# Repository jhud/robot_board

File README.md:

# Robot controller board

Controller board for building servo-based robots, such as hexapods.

Render of board rev 2

This project was designed to allow rapid prototyping of different types of servos and sensors for walking robots: it's easy to switch out different sensors, and I2C buses are exposed for adding standard plugin components, such as those from Adafruit. But the board could be used for any projects needing a lot of servos.

The main benefit of this over a standard Arduino is the number of PWM pins and the server sockets, plus the power supply monitoring circuitry.

You should be able to get a standard "spiderbot" Arduino sketch running on this hardware quite easily: I'll shortly publish some test sketches and controller firmware.

Have fun!

Board in action

## Features

Core features:
- ESP32 processor, Arduino compatible
- 32 PWM servo channels (ie max 10 legs)
- 6 foot contact sensors
- 7.6v LiPo battery, or power supply input
- Power supply monitoring for:
   - main battery voltage + current
   - 3.3v regulated rail voltage
   - 2x 5v rail servo voltages

With standard plugin modules installed in sockets:
- speech and audio output
- infrared beacon detection
- inertial measurement unit
- extra PWM channels

See it running here (video):

[http://www.youtube.com/watch?v=hFirgdrsIpw](https://www.youtube.com/watch?v=hFirgdrsIpw)

## Building it

### ESP32 CAM

The ESP32 CAM module can run on 3.3v or 5v. If you are getting freezes and dropped frames from the camera, try running it from the robot's 5v rail instead of 3.3v.

The ESP32 CAM has a XC6206-2.8V regulator after its 3.3v regulator, and this component has a dropout voltage up to ~500mV according to the specs. My hypothesis is that the camera crashes on slight undervoltages.

So the 3.3v rail must be rock solid - this may not be the case with your regulator, so it's generally recommended to run the ESP32 CAM off the 5v rail. Even with many noisy servos, the camera works fine on the robot on the 5v rail.

### Pullup resistors

Pullups can vary between 2K and 10K - if there are problems communicating with I2C, try reducing the pullups. Higher pull-ups waste less power.

## Revisions

Note that the main branch is a work in progress: please take an earlier revision if you want a working layout. These are tested and working (with some minor noise issues and a couple of bodge wires needed).

- main branch is a work in progress: I am upgrading to ESP32-S3 and have fixed some noise issues and minor annoyances. Use an older tag if you want something that works.
- 2nd revision: 32 PWM channels onboard, 6 foot switches + power pins for IR proximity sensors
- 1st revision: 16 PWM channels, 4 foot switches

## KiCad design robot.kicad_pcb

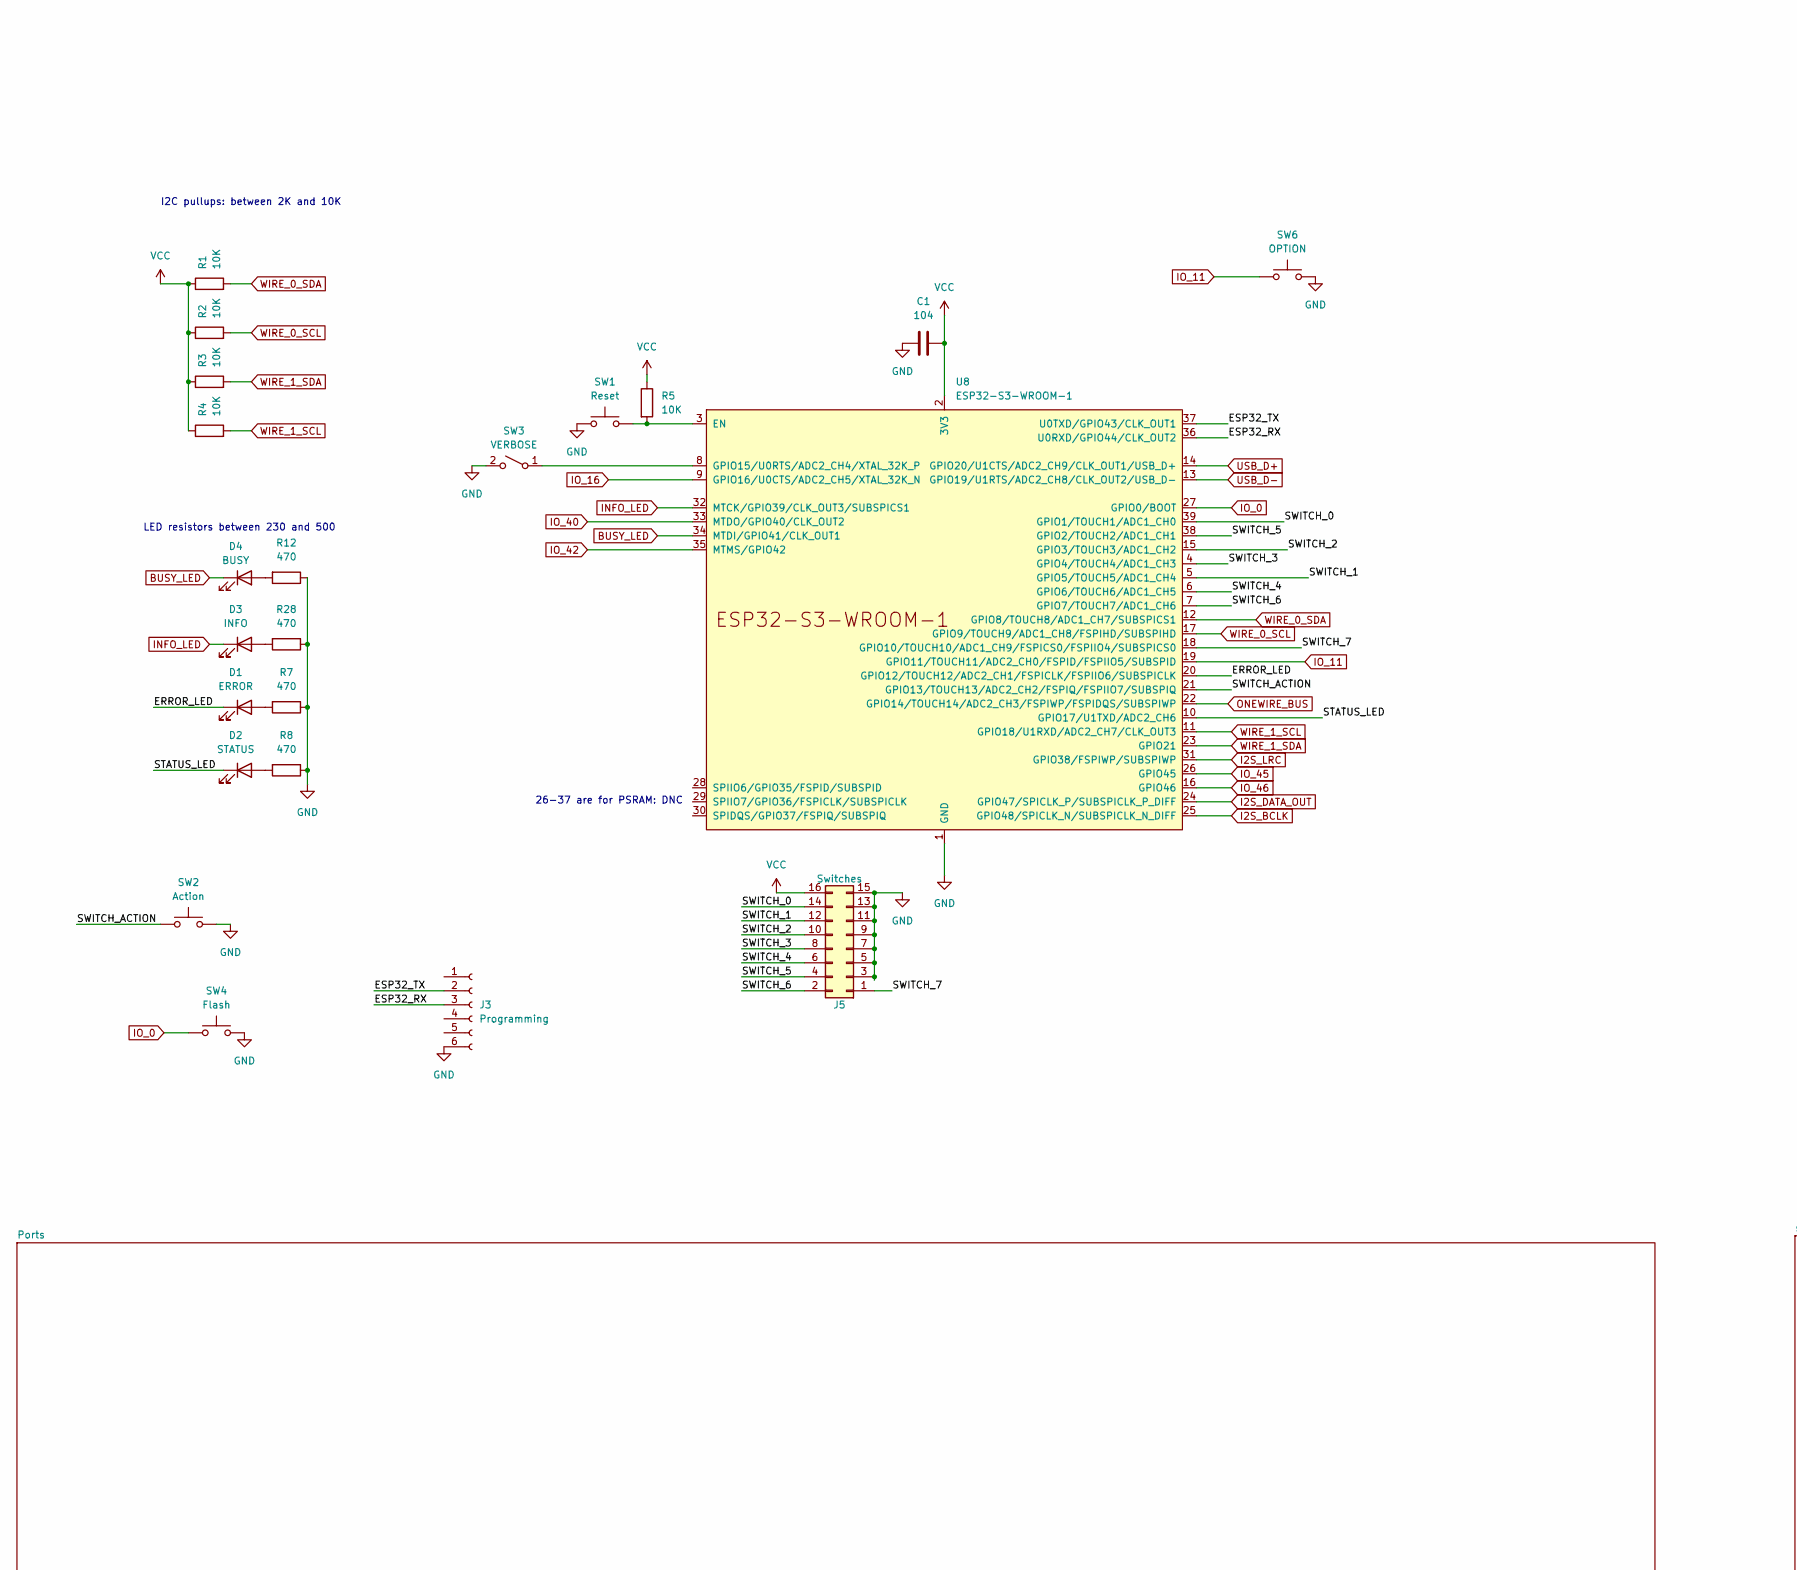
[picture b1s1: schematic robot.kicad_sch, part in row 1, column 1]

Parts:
C1: 104; C_1206_3216Metric_Pad1.33x1.80mm_HandSolder
D1: ERROR; LED_1206_3216Metric_Pad1.42x1.75mm_HandSolder
D2: STATUS; LED_1206_3216Metric_Pad1.42x1.75mm_HandSolder
D3: INFO; LED_1206_3216Metric_Pad1.42x1.75mm_HandSolder
D4: BUSY; LED_1206_3216Metric_Pad1.42x1.75mm_HandSolder
J3: Programming; PinSocket_1x06_P2.54mm_Vertical
J5: Switches; PinSocket_2x08_P2.54mm_Vertical
R1, R2, R3, R4, R5: 10K; R_1206_3216Metric_Pad1.30x1.75mm_HandSolder
R7, R8, R12, R28: 470; R_1206_3216Metric_Pad1.30x1.75mm_HandSolder
SW1: Reset; SW_SPST_CK_RS282G05A3
SW2: Action; SW_SPST_CK_RS282G05A3
SW3: VERBOSE; SW_Slide_1P2T_CK_OS102011MS2Q
SW4: Flash; SW_SPST_CK_RS282G05A3
SW6: OPTION; SW_SPST_CK_RS282G05A3
U8: ESP32-S3-WROOM-1; ESP32-S3-WROOM-1U

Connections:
/ERROR_LED: D1.1 (K), U8.20 (GPIO12/TOUCH12/ADC2_CH1/FSPICLK/FSPIIO6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)
/ESP32_RX: J3.3, U8.36 (U0RXD/GPIO44/CLK_OUT2)
/ESP32_TX: J3.2, U8.37 (U0TXD/GPIO43/CLK_OUT1)
/STATUS_LED: D2.1 (K), U8.10 (GPIO17/U1TXD/ADC2_CH6)
/SWITCH_0: J5.14, U8.39 (GPIO1/TOUCH1/ADC1_CH0)
/SWITCH_1: J5.12, U8.5 (GPIO5/TOUCH5/ADC1_CH4)
/SWITCH_2: J5.10, U8.15 (GPIO3/TOUCH3/ADC1_CH2)
/SWITCH_3: J5.8, U8.4 (GPIO4/TOUCH4/ADC1_CH3)
/SWITCH_4: J5.6, U8.6 (GPIO6/TOUCH6/ADC1_CH5)
/SWITCH_5: J5.4, U8.38 (GPIO2/TOUCH2/ADC1_CH1)
/SWITCH_6: J5.2, U8.7 (GPIO7/TOUCH7/ADC1_CH6)
/SWITCH_7: J5.1, U8.18 (GPIO10/TOUCH10/ADC1_CH9/FSPICS0/FSPIIO4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)
/SWITCH_ACTION: SW2.1, U8.21 (GPIO13/TOUCH13/ADC2_CH2/FSPIQ/FSPIIO7/S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)
BUSY_LED: D4.1 (K), U8.34 (MTDI/GPIO41/CLK_OUT1)
GND: C1.1, J3.6, J5.3, J5.5, J5.7, J5.9, J5.11, J5.13, J5.15, R7.1, R8.1, R12.1, R28.1, SW1.1, SW2.2, SW3.2 (B), SW4.2, SW6.2, U8.1 (GND), U8.40 (GND), U8.41 (GND); also elsewhere on the board
I2S_BCLK: U8.25 (GPIO48/SPICLK_N/SUBSPICLK_N_DIFF); also elsewhere on the board
I2S_DATA_OUT: U8.24 (GPIO47/SPICLK_P/SUBSPICLK_P_DIFF); also elsewhere on the board
I2S_LRC: U8.31 (GPIO38/FSPIWP/SUBSPIWP); also elsewhere on the board
INFO_LED: D3.1 (K), U8.32 (MTCK/GPIO39/CLK_OUT3/SUBSPICS1)
IO_0: SW4.1, U8.27 (GPIO0/BOOT)
IO_11: SW6.1, U8.19 (GPIO11/TOUCH11/ADC2_CH0/FSPID/FSPIIO5/S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)
IO_16: U8.9 (GPIO16/U0CTS/ADC2_CH5/XTAL_32K_N); also elsewhere on the board
IO_40: U8.33 (MTDO/GPIO40/CLK_OUT2); also elsewhere on the board
IO_42: U8.35 (MTMS/GPIO42); also elsewhere on the board
IO_45: U8.26 (GPIO45); also elsewhere on the board
IO_46: U8.16 (GPIO46); also elsewhere on the board
unnamed: D1.2 (A), R7.2
unnamed: D2.2 (A), R8.2
unnamed: D3.2 (A), R28.2
unnamed: D4.2 (A), R12.2
unnamed: SW3.1 (A), U8.8 (GPIO15/U0RTS/ADC2_CH4/XTAL_32K_P)
unnamed: R5.2, SW1.2, U8.3 (EN)
ONEWIRE_BUS: U8.22 (GPIO14/TOUCH14/ADC2_CH3/FSPIWP/FSPIDQS/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); also elsewhere on the board
USB_D+: U8.14 (GPIO20/U1CTS/ADC2_CH9/CLK_OUT1/USB_D+); also elsewhere on the board
USB_D-: U8.13 (GPIO19/U1RTS/ADC2_CH8/CLK_OUT2/USB_D-); also elsewhere on the board
VCC: C1.2, J5.16, R1.1, R2.1, R3.1, R4.1, R5.1, U8.2 (3V3); also elsewhere on the board
WIRE_0_SCL: R2.2, U8.17 (GPIO9/TOUCH9/ADC1_CH8/FSPIHD/SUBSPIHD); also elsewhere on the board
WIRE_0_SDA: R1.2, U8.12 (GPIO8/TOUCH8/ADC1_CH7/SUBSPICS1); also elsewhere on the board

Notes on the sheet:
26-37 are for PSRAM: DNC
LED resistors between 230 and 500
I2C pullups: between 2K and 10K

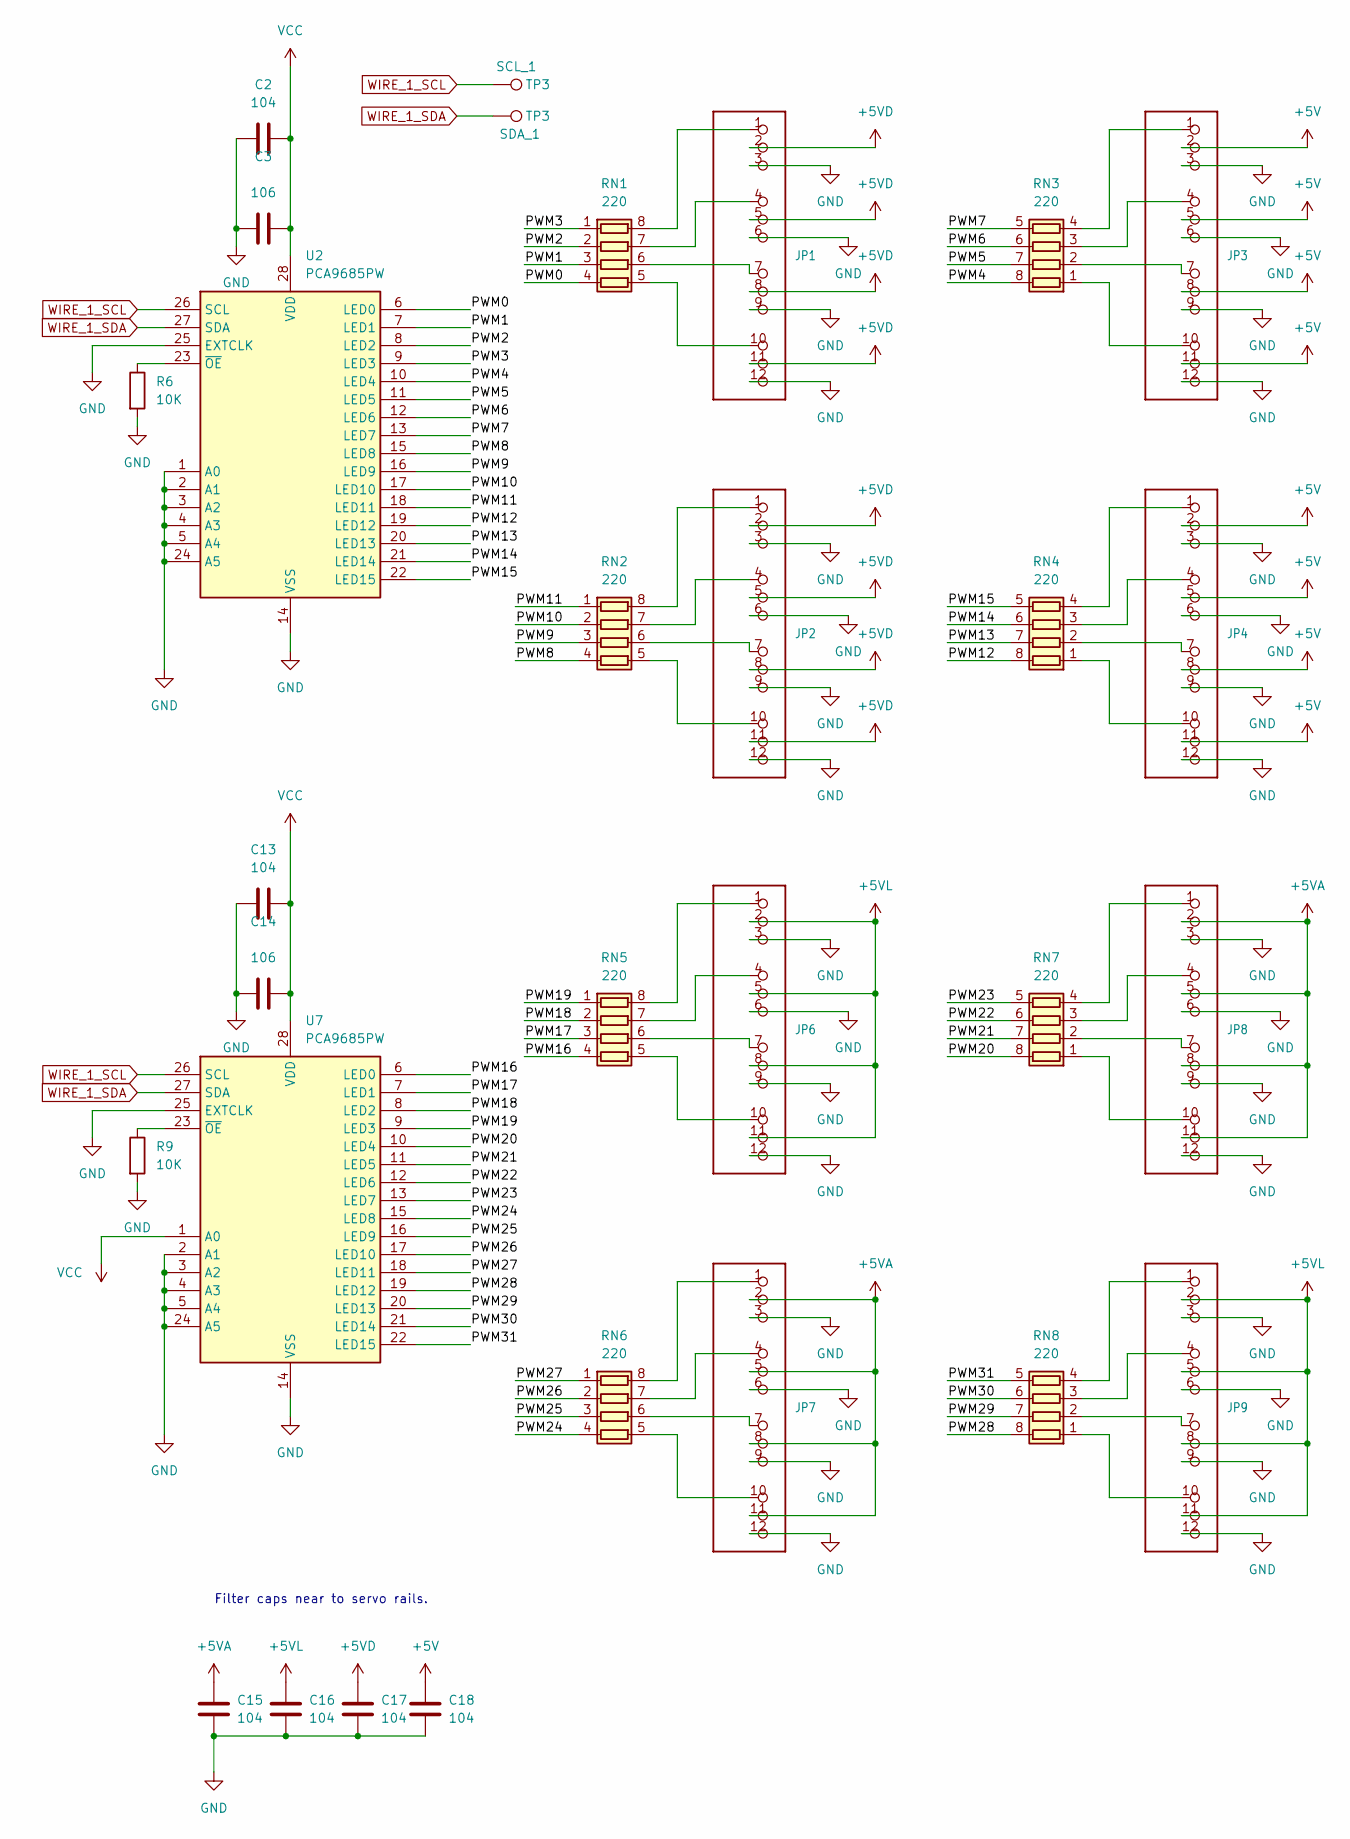
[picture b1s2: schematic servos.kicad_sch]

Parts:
C2, C13, C15, C16, C17, C18: 104; C_1206_3216Metric_Pad1.33x1.80mm_HandSolder
C3, C14: 106; C_1210_3225Metric_Pad1.33x2.70mm_HandSolder
JP1, JP2, JP3, JP4, JP6, JP7, JP8, JP9: HEADER-3X04; 3X04
R6, R9: 10K; R_1206_3216Metric_Pad1.30x1.75mm_HandSolder
RN1, RN2, RN3, RN4, RN5, RN6, RN7, RN8: 220; R_Array_Concave_4x0603
TP3: SCL_1; TestPoint_Pad_D2.0mm
U2, U7: PCA9685PW; TSSOP-28_4.4x9.7mm_P0.65mm

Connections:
+5V: C18.1, JP3.2, JP3.5, JP3.8, JP3.11, JP4.2, JP4.5, JP4.8, JP4.11; also elsewhere on the board
+5VD: C17.1, JP1.2, JP1.5, JP1.8, JP1.11, JP2.2, JP2.5, JP2.8, JP2.11; also elsewhere on the board
+5VL: C16.1, JP6.2, JP6.5, JP6.8, JP6.11, JP9.2, JP9.5, JP9.8, JP9.11; also elsewhere on the board
/servos/PWM0: RN1.4 (R4.1), U2.6 (LED0)
/servos/PWM1: RN1.3 (R3.1), U2.7 (LED1)
/servos/PWM2: RN1.2 (R2.1), U2.8 (LED2)
/servos/PWM3: RN1.1 (R1.1), U2.9 (LED3)
/servos/PWM4: RN3.8 (R1.2), U2.10 (LED4)
/servos/PWM5: RN3.7 (R2.2), U2.11 (LED5)
/servos/PWM6: RN3.6 (R3.2), U2.12 (LED6)
/servos/PWM7: RN3.5 (R4.2), U2.13 (LED7)
/servos/PWM8: RN2.4 (R4.1), U2.15 (LED8)
/servos/PWM9: RN2.3 (R3.1), U2.16 (LED9)
/servos/PWM10: RN2.2 (R2.1), U2.17 (LED10)
/servos/PWM11: RN2.1 (R1.1), U2.18 (LED11)
/servos/PWM12: RN4.8 (R1.2), U2.19 (LED12)
/servos/PWM13: RN4.7 (R2.2), U2.20 (LED13)
/servos/PWM14: RN4.6 (R3.2), U2.21 (LED14)
/servos/PWM15: RN4.5 (R4.2), U2.22 (LED15)
/servos/PWM16: RN5.4 (R4.1), U7.6 (LED0)
/servos/PWM17: RN5.3 (R3.1), U7.7 (LED1)
/servos/PWM18: RN5.2 (R2.1), U7.8 (LED2)
/servos/PWM19: RN5.1 (R1.1), U7.9 (LED3)
/servos/PWM20: RN7.8 (R1.2), U7.10 (LED4)
/servos/PWM21: RN7.7 (R2.2), U7.11 (LED5)
/servos/PWM22: RN7.6 (R3.2), U7.12 (LED6)
/servos/PWM23: RN7.5 (R4.2), U7.13 (LED7)
/servos/PWM24: RN6.4 (R4.1), U7.15 (LED8)
/servos/PWM25: RN6.3 (R3.1), U7.16 (LED9)
/servos/PWM26: RN6.2 (R2.1), U7.17 (LED10)
/servos/PWM27: RN6.1 (R1.1), U7.18 (LED11)
/servos/PWM28: RN8.8 (R1.2), U7.19 (LED12)
/servos/PWM29: RN8.7 (R2.2), U7.20 (LED13)
/servos/PWM30: RN8.6 (R3.2), U7.21 (LED14)
/servos/PWM31: RN8.5 (R4.2), U7.22 (LED15)
GND: C2.2, C3.1, C13.2, C14.1, C15.2, C16.2, C17.2, C18.2, JP1.3, JP1.6, JP1.9, JP1.12, JP2.3, JP2.6, JP2.9, JP2.12, JP3.3, JP3.6, JP3.9, JP3.12, JP4.3, JP4.6, JP4.9, JP4.12, JP6.3, JP6.6, JP6.9, JP6.12, JP7.3, JP7.6, JP7.9, JP7.12, JP8.3, JP8.6, JP8.9, JP8.12, JP9.3, JP9.6, JP9.9, JP9.12, R6.2, R9.2, U2.1 (A0), U2.2 (A1), U2.3 (A2), U2.4 (A3), U2.5 (A4), U2.14 (VSS), U2.24 (A5), U2.25 (EXTCLK), U7.2 (A1), U7.3 (A2), U7.4 (A3), U7.5 (A4), U7.14 (VSS), U7.24 (A5), U7.25 (EXTCLK); also elsewhere on the board
unnamed: JP1.1, RN1.8 (R1.2)
unnamed: JP1.4, RN1.7 (R2.2)
unnamed: JP1.7, RN1.6 (R3.2)
unnamed: JP1.10, RN1.5 (R4.2)
unnamed: JP2.1, RN2.8 (R1.2)
unnamed: JP2.4, RN2.7 (R2.2)
unnamed: JP2.7, RN2.6 (R3.2)
unnamed: JP2.10, RN2.5 (R4.2)
unnamed: JP3.10, RN3.1 (R1.1)
unnamed: JP3.7, RN3.2 (R2.1)
unnamed: JP3.4, RN3.3 (R3.1)
unnamed: JP3.1, RN3.4 (R4.1)
unnamed: JP4.10, RN4.1 (R1.1)
unnamed: JP4.7, RN4.2 (R2.1)
unnamed: JP4.4, RN4.3 (R3.1)
unnamed: JP4.1, RN4.4 (R4.1)
unnamed: JP6.1, RN5.8 (R1.2)
unnamed: JP6.4, RN5.7 (R2.2)
unnamed: JP6.7, RN5.6 (R3.2)
unnamed: JP6.10, RN5.5 (R4.2)
unnamed: JP7.1, RN6.8 (R1.2)
unnamed: JP7.4, RN6.7 (R2.2)
unnamed: JP7.7, RN6.6 (R3.2)
unnamed: JP7.10, RN6.5 (R4.2)
unnamed: JP8.10, RN7.1 (R1.1)
unnamed: JP8.7, RN7.2 (R2.1)
unnamed: JP8.4, RN7.3 (R3.1)
unnamed: JP8.1, RN7.4 (R4.1)
unnamed: JP9.10, RN8.1 (R1.1)
unnamed: JP9.7, RN8.2 (R2.1)
unnamed: JP9.4, RN8.3 (R3.1)
unnamed: JP9.1, RN8.4 (R4.1)
unnamed: R6.1, U2.23 (~OE)
unnamed: R9.1, U7.23 (~OE)
VCC: C2.1, C3.2, C13.1, C14.2, U2.28 (VDD), U7.1 (A0), U7.28 (VDD); also elsewhere on the board

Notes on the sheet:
Filter caps near to servo rails.

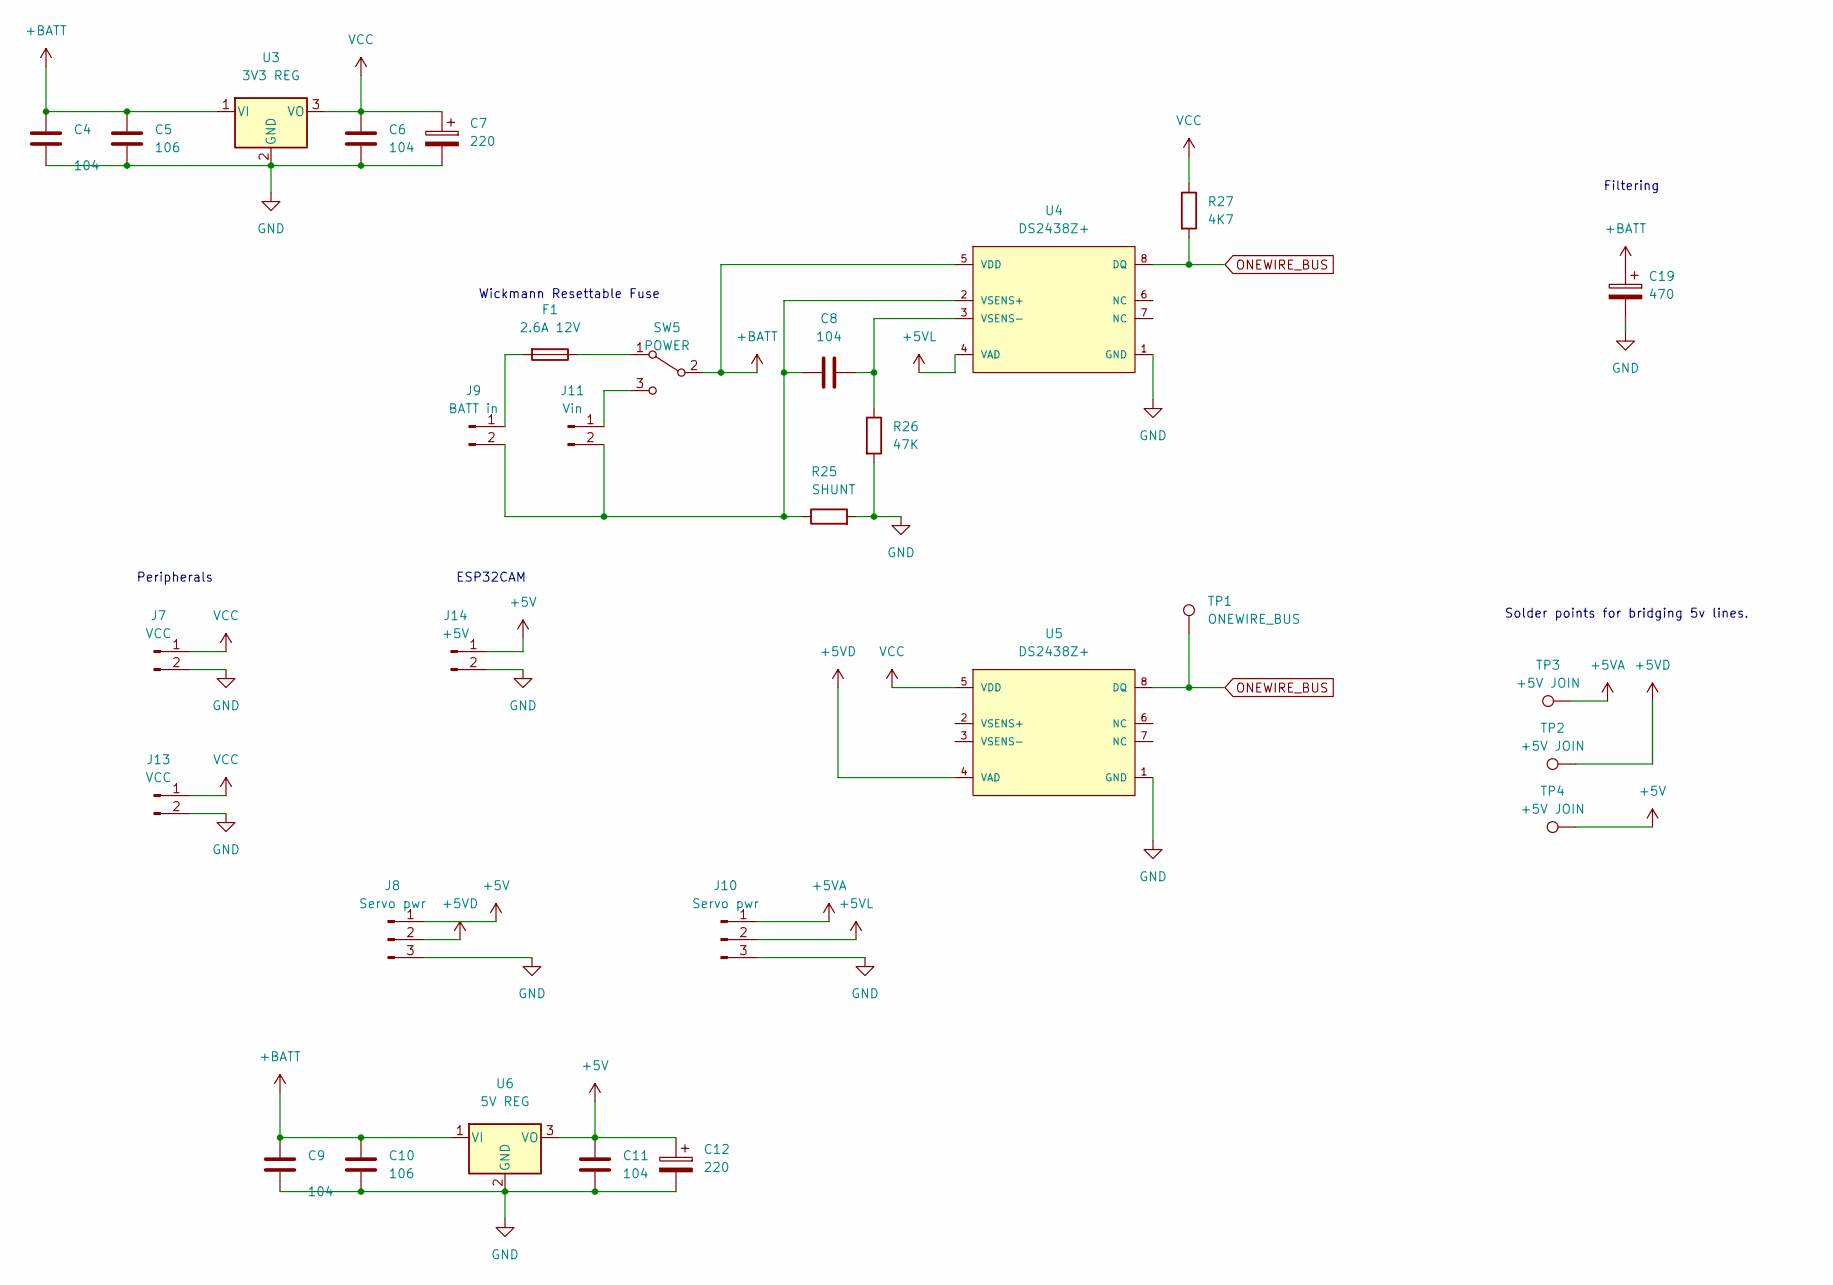
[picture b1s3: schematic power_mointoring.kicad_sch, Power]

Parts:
C4, C6, C8, C9, C11: 104; C_1206_3216Metric_Pad1.33x1.80mm_HandSolder
C5, C10: 106; C_1210_3225Metric_Pad1.33x2.70mm_HandSolder
C7, C12: 220; C_Elec_6.3x5.4
C19: 470; C_Elec_6.3x7.7
F1: 2.6A 12V; Fuse_2010_5025Metric
J7, J13: VCC; PinHeader_1x02_P2.54mm_Vertical
J8, J10: Servo pwr; Connector_SolderPadsx3
J9: BATT in; JST_VH_B2P-VH-B_1x02_P3.96mm_Vertical
J11: Vin; JST_VH_B2P-VH-B_1x02_P3.96mm_Vertical
J14: +5V; PinHeader_1x02_P2.54mm_Vertical
R25: SHUNT; R_1812_4532Metric_Pad1.30x3.40mm_HandSolder
R26: 47K; R_1206_3216Metric_Pad1.30x1.75mm_HandSolder
R27: 4K7; R_1206_3216Metric_Pad1.30x1.75mm_HandSolder
SW5: POWER; Switch-SS12F23
TP1: ONEWIRE_BUS; TestPoint_Pad_D2.0mm
TP2, TP3, TP4: +5V JOIN; TestPoint_Pad_D2.0mm
U3: 3V3 REG; TO-220-3_Vertical
U4, U5: DS2438Z+; Maxim-S8-5-0-P-IPC_A; mouser part number 700-DS2438Z; digikey description IC MONITOR SMART BATTERY 8-SOIC
U6: 5V REG; TO-220-3_Vertical

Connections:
+5V: C11.1, C12.1, J8.1, J14.1, TP4.1, U6.3 (VO); also elsewhere on the board
+5VD: J8.2, TP2.1, U5.4 (VAD); also elsewhere on the board
+5VL: J10.2, U4.4 (VAD); also elsewhere on the board
+BATT: C4.1, C5.1, C9.1, C10.1, C19.1, SW5.2 (B), U3.1 (VI), U4.5 (VDD), U6.1 (VI)
GND: C4.2, C5.2, C6.2, C7.2, C9.2, C10.2, C11.2, C12.2, C19.2, J7.2, J8.3, J10.3, J13.2, J14.2, R25.2, R26.2, U3.2 (GND), U4.1 (GND), U5.1 (GND), U6.2 (GND); also elsewhere on the board
unnamed: F1.2, J9.1
unnamed: J11.1, SW5.3 (C)
unnamed: C8.2, J9.2, J11.2, R25.1, U4.2 (VSENS+)
unnamed: F1.1, SW5.1 (A)
unnamed: C8.1, R26.1, U4.3 (VSENS-)
ONEWIRE_BUS: R27.2, TP1.1, U4.8 (DQ), U5.8 (DQ); also elsewhere on the board
VCC: C6.1, C7.1, J7.1, J13.1, R27.1, U3.3 (VO), U5.5 (VDD); also elsewhere on the board

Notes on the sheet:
Filtering
ESP32CAM
Solder points for bridging 5v lines.
Wickmann Resettable Fuse
Peripherals

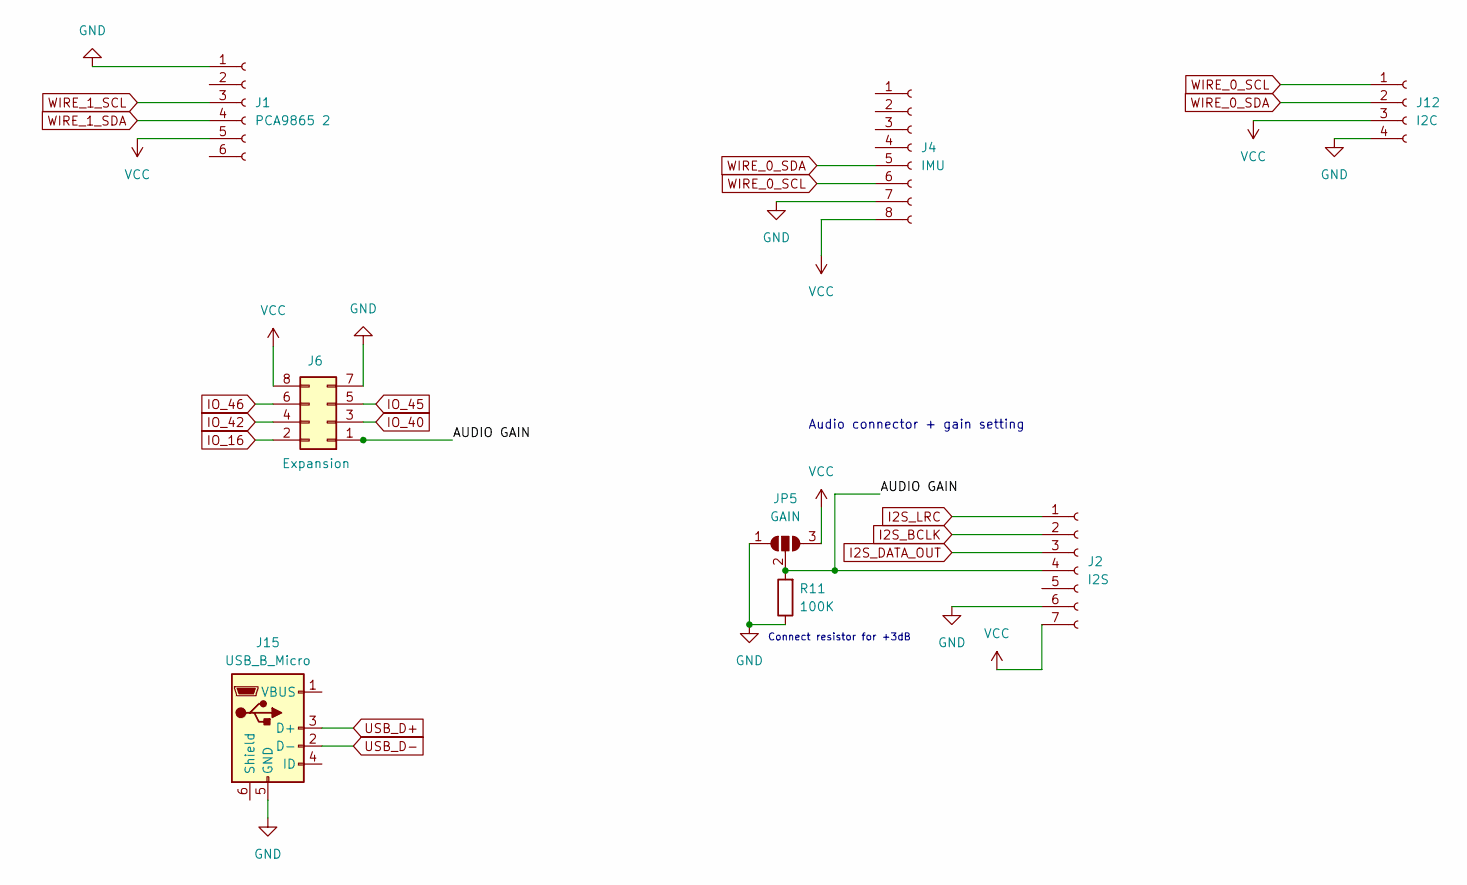
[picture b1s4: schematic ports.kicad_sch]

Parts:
J1: PCA9865 2; PinSocket_1x06_P2.54mm_Vertical
J2: I2S; PinSocket_1x07_P2.54mm_Vertical
J4: IMU; PinSocket_1x08_P2.54mm_Vertical
J6: Expansion; PinSocket_2x04_P2.54mm_Vertical
J12: I2C; PinSocket_1x04_P2.54mm_Vertical
J15: USB_B_Micro; USB_Micro-B_Amphenol_10104110_Horizontal
JP5: GAIN; SolderJumper-3_P1.3mm_Open_RoundedPad1.0x1.5mm
R11: 100K; R_1206_3216Metric_Pad1.30x1.75mm_HandSolder

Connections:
/Ports/AUDIO GAIN: J2.4, J6.1, JP5.2 (C), R11.2
GND: J1.1, J2.6, J4.7, J6.7, J12.4, J15.5 (GND), JP5.1 (A), R11.1; also elsewhere on the board
I2S_BCLK: J2.2; also elsewhere on the board
I2S_DATA_OUT: J2.3; also elsewhere on the board
I2S_LRC: J2.1; also elsewhere on the board
IO_16: J6.2; also elsewhere on the board
IO_40: J6.3; also elsewhere on the board
IO_42: J6.4; also elsewhere on the board
IO_45: J6.5; also elsewhere on the board
IO_46: J6.6; also elsewhere on the board
USB_D+: J15.3 (D+); also elsewhere on the board
USB_D-: J15.2 (D-); also elsewhere on the board
VCC: J1.5, J2.7, J4.8, J6.8, J12.3, JP5.3 (B); also elsewhere on the board
WIRE_0_SCL: J4.6, J12.1; also elsewhere on the board
WIRE_0_SDA: J4.5, J12.2; also elsewhere on the board

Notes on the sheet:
Connect resistor for +3dB
Audio connector + gain setting

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
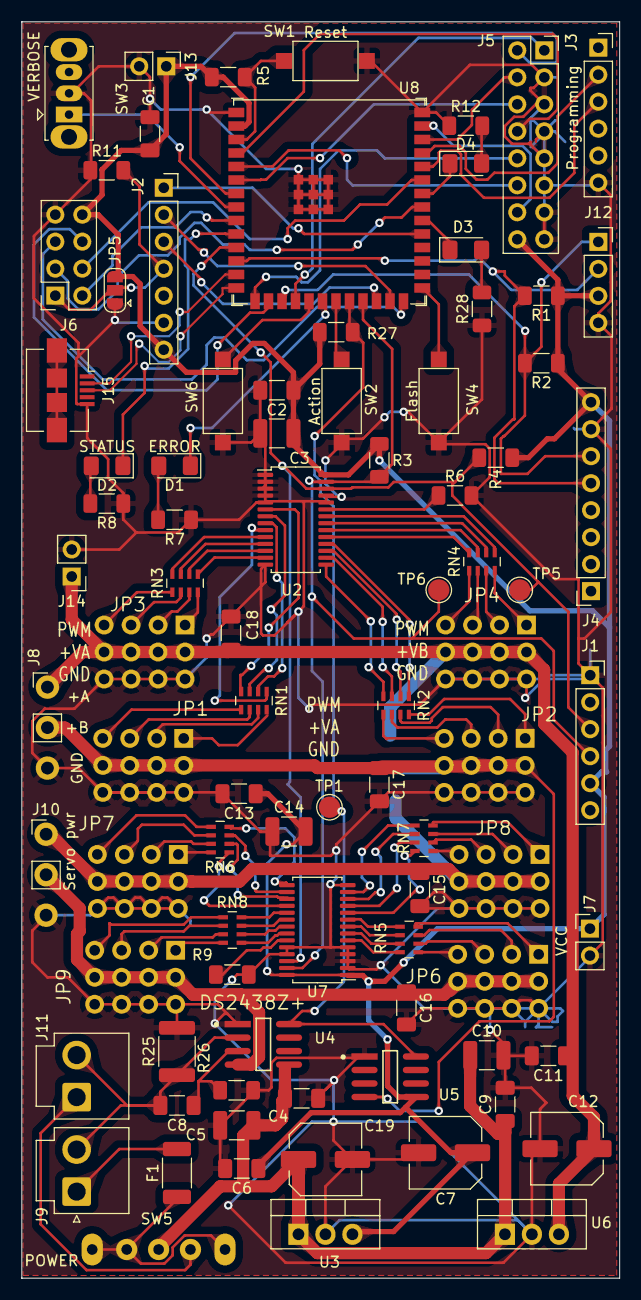
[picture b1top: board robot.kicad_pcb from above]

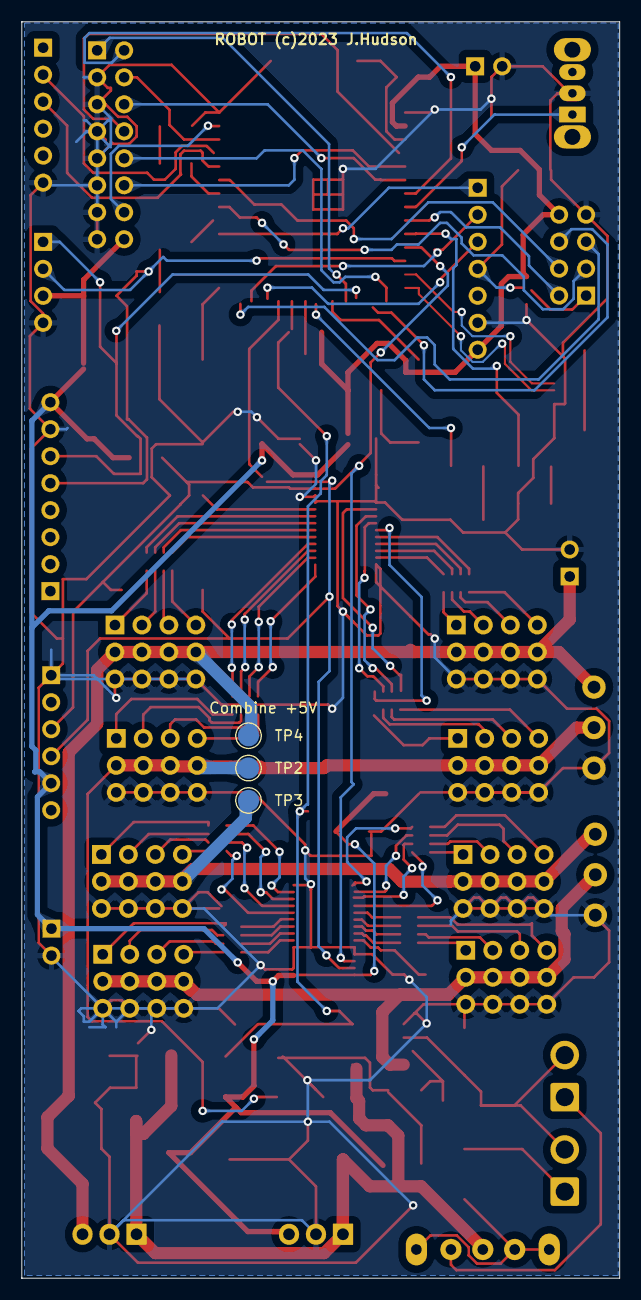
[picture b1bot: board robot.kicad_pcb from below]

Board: 2 copper layers, 56.3 x 118.2 mm, 90 parts (3 on the bottom side), 117 nets.

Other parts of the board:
TP5: SCL_1; TestPoint_Pad_D2.0mm
TP6: SDA_1; TestPoint_Pad_D2.0mm

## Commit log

2022-12-30 Layed out board, not routed
2022-12-30 Added extra mounting hole
2022-12-30 Ready to route.
2022-12-31 Ready for fab.
2023-01-15 Added minor footprint changes after trying to build the board. Added pin to switch battery to Vin.
2023-02-22 Added extra pins and input from revision 1.
2023-02-28 Added revision 2 features, not routed.
2023-02-28 Board ready to go.
2023-02-28 Clean chematic
2023-03-02 Cleaned revision 2.
2023-05-09 Very minor tweaks for board version 3.
2023-06-13 Upgrade to version 7, started adding new WROOM-S3
2023-06-15 started wiring up s3
2023-10-02 Added larger filter caps + across the battery
2023-10-02 Added readme
2023-10-02 Resized images
2023-10-02 Create LICENSE
2023-10-04 Added info about ESP32 CAM.
2023-10-04 Removed old ESP32, added ESP32 S3.
2023-10-05 Finished routing board revision 3: ready for first PCB run.
2023-10-06 Sent off for fabrication, added test points.
2023-10-29 Switched out GPIO3 for GPIO16 because it is a strapping pin with no pullup.
2023-10-30 Added missing power bridge point for 1 rail.
2023-11-14 Switched a few pins which were glitchy in on the hardware to known good pins. May have just been a faulty ESP32, but just to be sure.
2023-11-18 Flipped current sense resistor connections - it was the wrong way around.

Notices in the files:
robot.kicad_pcb:
ROBOT (c)2023 J.Hudson
